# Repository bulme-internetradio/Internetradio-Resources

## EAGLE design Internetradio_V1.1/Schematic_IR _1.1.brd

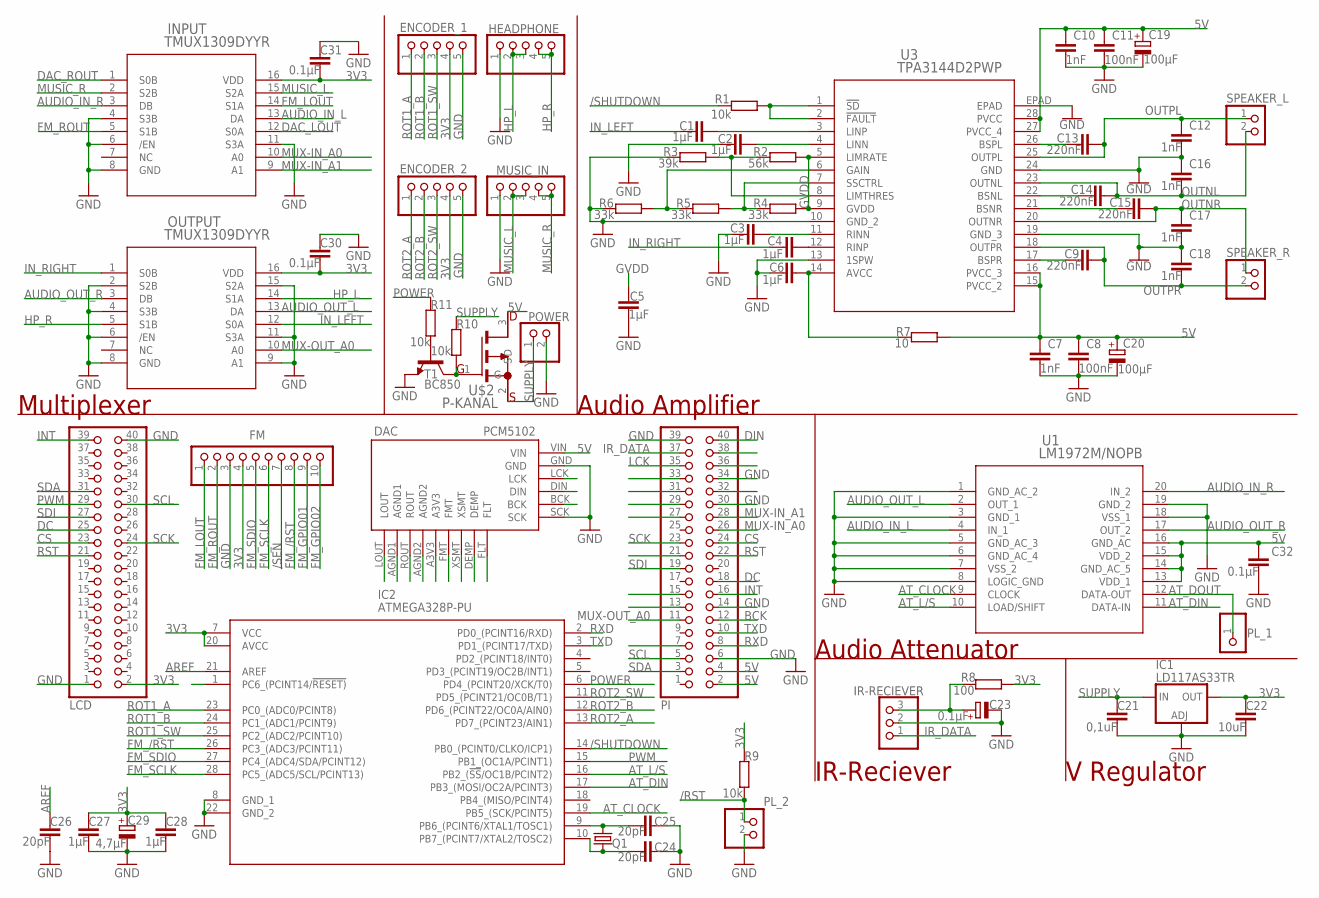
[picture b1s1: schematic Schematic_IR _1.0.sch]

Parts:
C1, C2, C3, C4, C5, C6, C27, C28: 1µF; C0603K
C7, C10, C12, C16, C17, C18: 1nF; C0603K
C8, C11: 100nF; C0603K
C9, C13, C14, C15: 220nF; C0603K
C19, C20: 100µF; SMC_B
C21: 0,1uF; C0603K
C22: 10uF; C0603K
C23: 0.1µF; SMC_B
C24, C25, C26: 20pF; C0603K
C29: 4,7µF; SMC_B
C30, C31, C32: 0.1µF; C0603K
DAC: PCM5102
ENCODER_1, ENCODER_2: PINHD-1X5; 1X05
FM: PINHD-1X10_2.54; 1X10
HEADPHONE: PINHD-1X5_2.54; 1X05
IC1: LD117AS33TR; SOT223
IC2: ATMEGA328P-PU; DIP794W53P254L3467H457Q28N
INPUT: TMUX1309DYYR; SOIC_309DYYR_TEX
IR-RECIEVER: PINHD-1X3_2.54; 1X03
LCD: PINHD-2X20; 2X20
MUSIC_IN: PINHD-1X5_2.54; 1X05
OUTPUT: TMUX1309DYYR; SOIC_309DYYR_TEX
PI: PINHD-2X20; 2X20
PL_1: PINHD-1X1_2.00; 1X01M
PL_2: PINHD-1X2_2.00; 1X02M
POWER: PINHD-1X2_2.54; 1X02
Q1: KX-KS; 11.4X4.5
R1, R9, R10, R11: 10k; R0603
R2: 56k; R0603
R3: 39k; R0603
R4, R5, R6: 33k; R0603
R7: 10; R0603
R8: 100; R0603
SPEAKER_L: PINHD-1X2_2.54; 1X02
SPEAKER_R: PINHD-1X2_2.54; 1X02
T1: BC850; SOT23
U1: LM1972M/NOPB; M20B_TEX
U3: TPA3144D2PWP; PWP28_2P4X3.4_TEX
U$2: P-KANAL; SOT23

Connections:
3V3: C22.2, C27.1, C28.1, C29.+, C30.2, C31.2, ENCODER_1.4, ENCODER_2.4, FM.4, IC1.4 (OUT), IC2.7 (VCC), IC2.20 (AVCC), INPUT.16 (VDD), LCD.2, OUTPUT.16 (VDD), R8.2, R9.2
5V: C7.1, C8.1, C10.1, C11.1, C19.+, C20.+, C32.1, DAC.VIN, PI.2, PI.4, R7.2, U1.13 (VDD_1), U1.14 (GND_AC_5), U1.15 (VDD_2), U1.16 (GND_AC), U3.15 (PVCC_2), U3.16 (PVCC_3), U3.27 (PVCC_4), U3.28 (PVCC), U$2.3 (D)
/RST: IC2.1 (PC6_(PCINT14/!RESET)), PL_2.1, R9.1
/SEN: FM.7
/SHUTDOWN: IC2.14 (PB0_(PCINT0/CLKO/ICP1)), R1.1
AREF: C26.1, IC2.21 (AREF)
AT_CLOCK: IC2.19 (PB5_(SCK/PCINT5)), U1.9 (CLOCK)
AT_DIN: IC2.17 (PB3_(MOSI/OC2A/PCINT3)), U1.11 (DATA-IN)
AT_DOUT: PL_1.1, U1.12 (DATA-OUT)
AT_L/S: IC2.16 (PB2_(!SS!/OC1B/PCINT2)), U1.10 (LOAD/SHIFT)
AUDIO_IN_L: INPUT.13 (DA), U1.4 (IN_1)
AUDIO_IN_R: INPUT.3 (DB), U1.20 (IN_2)
AUDIO_OUT_L: OUTPUT.13 (DA), U1.2 (OUT_1)
AUDIO_OUT_R: OUTPUT.3 (DB), U1.17 (OUT_2)
BCK: DAC.BCK, PI.12
CS: LCD.23, PI.24
DAC_LOUT: DAC.LOUT, INPUT.12 (S0A)
DAC_ROUT: DAC.ROUT, INPUT.1 (S0B)
DC: LCD.25, PI.18
DIN: DAC.DIN, PI.40
FM_/RST: FM.8, IC2.26 (PC3_(ADC3/PCINT11))
FM_GPIO01: FM.9
FM_GPIO02: FM.10
FM_LOUT: FM.1, INPUT.14 (S1A)
FM_ROUT: FM.2, INPUT.5 (S1B)
FM_SCLK: FM.6, IC2.28 (PC5_(ADC5/SCL/PCINT13))
FM_SDIO: FM.5, IC2.27 (PC4_(ADC4/SDA/PCINT12))
GND: C2.1, C3.1, C5.2, C6.1, C7.2, C8.2, C10.2, C11.2, C12.2, C16.1, C17.2, C18.1, C19.-, C20.-, C21.1, C22.1, C23.-, C24.1, C25.1, C26.2, C27.2, C28.2, C29.-, C30.1, C31.1, C32.2, DAC.GND, DAC.SCK, ENCODER_1.5, ENCODER_2.5, FM.3, HEADPHONE.1, IC1.1 (ADJ), IC2.8 (GND_1), IC2.22 (GND_2), INPUT.4 (S3B), INPUT.6 (/EN), INPUT.8 (GND), INPUT.11 (S3A), IR-RECIEVER.2, LCD.1, LCD.40, MUSIC_IN.1, OUTPUT.2 (S2B), OUTPUT.4 (S3B), OUTPUT.6 (/EN), OUTPUT.8 (GND), OUTPUT.9 (A1), OUTPUT.11 (S3A), OUTPUT.15 (S2A), PI.6, PI.14, PI.30, PI.34, PI.39, PL_2.2, POWER.2, R3.1, R6.1, T1.2 (E), U1.1 (GND_AC_2), U1.3 (GND_1), U1.5 (GND_AC_3), U1.6 (GND_AC_4), U1.7 (VSS_2), U1.8 (LOGIC_GND), U1.18 (VSS_1), U1.19 (GND_2), U3.10 (GND_2), U3.13 (1SPW), U3.19 (GND_3), U3.24 (GND), U3.EPAD
GVDD: C5.1, R2.2, R4.2, U3.5 (LIMRATE), U3.9 (GVDD)
HP_L: HEADPHONE.2, HEADPHONE.3, OUTPUT.14 (S1A)
HP_R: HEADPHONE.4, HEADPHONE.5, OUTPUT.5 (S1B)
INT: LCD.39, PI.16
IN_LEFT: C1.1, OUTPUT.12 (S0A)
IN_RIGHT: C4.1, OUTPUT.1 (S0B)
IR_DATA: IR-RECIEVER.1, PI.37
LCK: DAC.LCK, PI.35
MUSIC_L: INPUT.15 (S2A), MUSIC_IN.2, MUSIC_IN.3
MUSIC_R: INPUT.2 (S2B), MUSIC_IN.4, MUSIC_IN.5
MUX-IN_A0: INPUT.10 (A0), PI.26
MUX-IN_A1: INPUT.9 (A1), PI.28
MUX-OUT_A0: OUTPUT.10 (A0), PI.11
unnamed: R1.2, U3.1 (!SD), U3.2 (!FAULT)
unnamed: C4.2, U3.12 (RINP)
unnamed: R11.2, T1.1 (B)
unnamed: R4.1, R5.2, U3.7 (SSCTRL)
unnamed: R2.1, R3.2, U3.8 (LIMTHRES)
unnamed: R5.1, R6.2, U3.6 (GAIN)
unnamed: C6.2, R7.1, U3.14 (AVCC)
unnamed: R10.1, T1.3 (C), U$2.1 (G)
unnamed: C24.2, IC2.10 (PB7_(PCINT7/XTAL2/TOSC2)), Q1.1
unnamed: C25.2, IC2.9 (PB6_(PCINT6/XTAL1/TOSC1)), Q1.2
unnamed: C1.2, U3.3 (LINP)
unnamed: C2.2, U3.4 (LINN)
unnamed: C13.1, U3.26 (BSPL)
unnamed: C23.+, IR-RECIEVER.3, R8.1
unnamed: C3.2, U3.11 (RINN)
unnamed: C14.1, U3.22 (BSNL)
unnamed: C15.1, U3.21 (BSNR)
unnamed: C9.1, U3.17 (BSPR)
OUTNL: C14.2, C16.2, SPEAKER_L.2, U3.23 (OUTNL)
OUTNR: C15.2, C17.1, SPEAKER_R.1, U3.20 (OUTNR)
OUTPL: C12.1, C13.2, SPEAKER_L.1, U3.25 (OUTPL)
OUTPR: C9.2, C18.2, SPEAKER_R.2, U3.18 (OUTPR)
POWER: IC2.6 (PD4_(PCINT20/XCK/T0)), R11.1
PWM: IC2.15 (PB1_(OC1A/PCINT1)), LCD.29
ROT1_A: ENCODER_1.1, IC2.23 (PC0_(ADC0/PCINT8))
ROT1_B: ENCODER_1.2, IC2.24 (PC1_(ADC1/PCINT9))
ROT1_SW: ENCODER_1.3, IC2.25 (PC2_(ADC2/PCINT10))
ROT2_A: ENCODER_2.1, IC2.13 (PD7_(PCINT23/AIN1))
ROT2_B: ENCODER_2.2, IC2.12 (PD6_(PCINT22/OC0A/AIN0))
ROT2_SW: ENCODER_2.3, IC2.11 (PD5_(PCINT21/OC0B/T1))
RST: LCD.21, PI.22
RXD: IC2.2 (PD0_(PCINT16/RXD)), PI.8
SCK: LCD.24, PI.23
SCL: LCD.30, PI.5
SDA: LCD.31, PI.3
SDI: LCD.27, PI.19
SUPPLY: C21.2, IC1.3 (IN), POWER.1, R10.2, U$2.2 (S)
TXD: IC2.3 (PD1_(PCINT17/TXD)), PI.10

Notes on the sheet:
Multiplexer
Audio Amplifier
Audio Attenuator
V Regulator
IR-Reciever

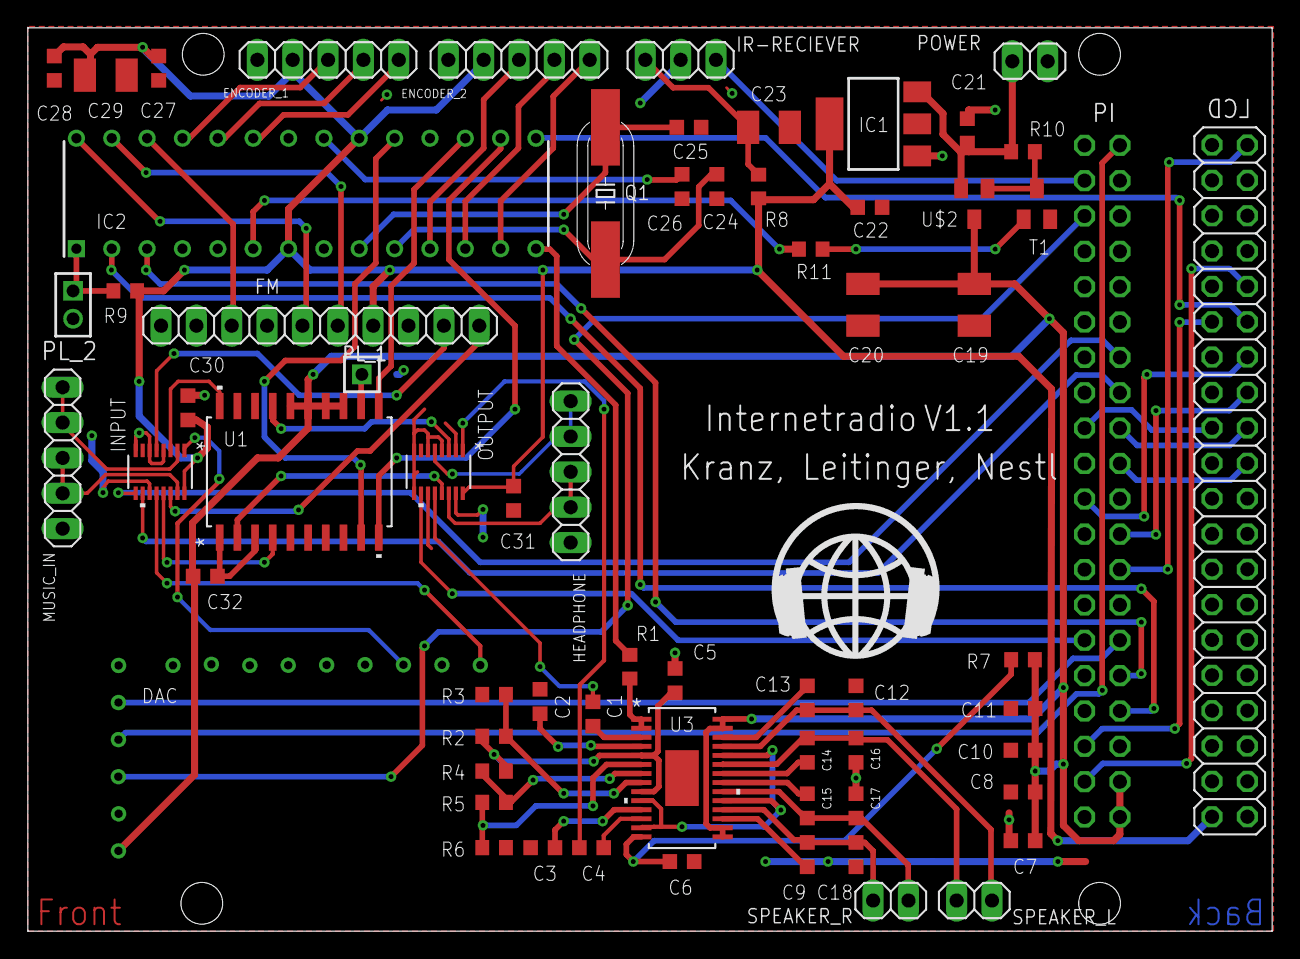
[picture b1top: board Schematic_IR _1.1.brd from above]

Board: 2 copper layers, 89.4 x 64.9 mm, 67 parts (1 on the bottom side), 76 nets.

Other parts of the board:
U$1: LOGO

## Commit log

2021-04-21 Create ert
2021-04-21 reorganised files
2021-04-21 reorganised again
2021-04-21 added new files
2021-04-21 updated name
2021-04-21 added file to laser
2021-04-21 added new data

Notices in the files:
parts and their libraries:
Fancy_InternetRadio: COPYRIGHT: Copyright (C) 2018 Accelerated Designs. All rights reserved
crystal-geyer_V1_0: Copyright: Geyer-Electronic
